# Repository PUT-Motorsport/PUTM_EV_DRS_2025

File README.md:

# PUTM_EV_DRS_2024
 Drs (active aero) project for PUT Motorsport

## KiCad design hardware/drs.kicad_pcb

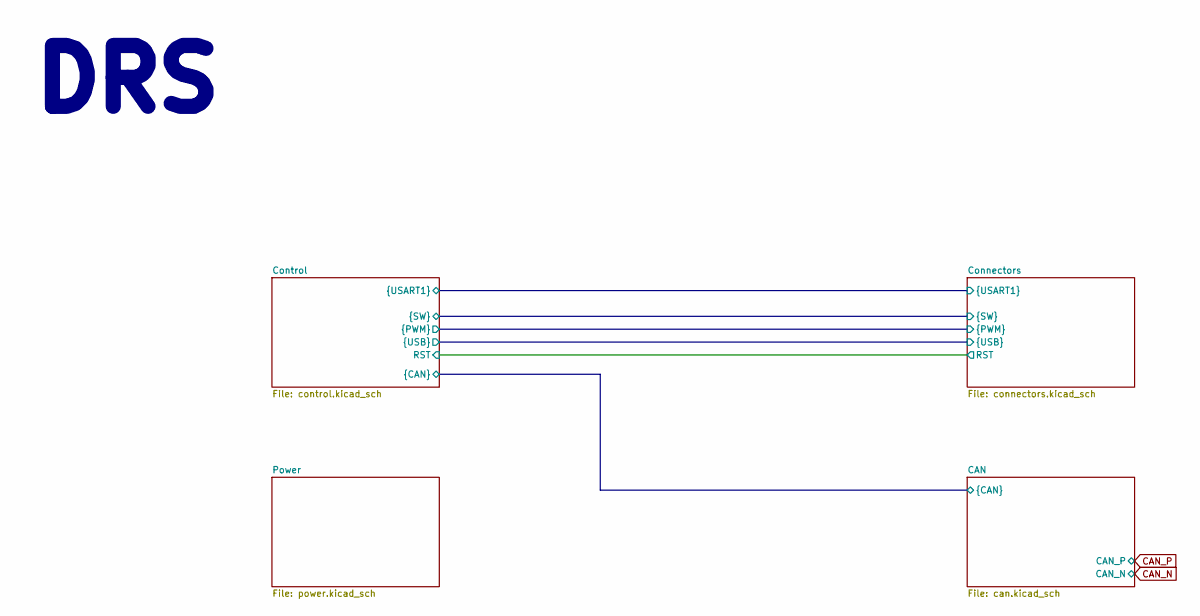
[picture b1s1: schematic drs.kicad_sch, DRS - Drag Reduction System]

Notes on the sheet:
DRS

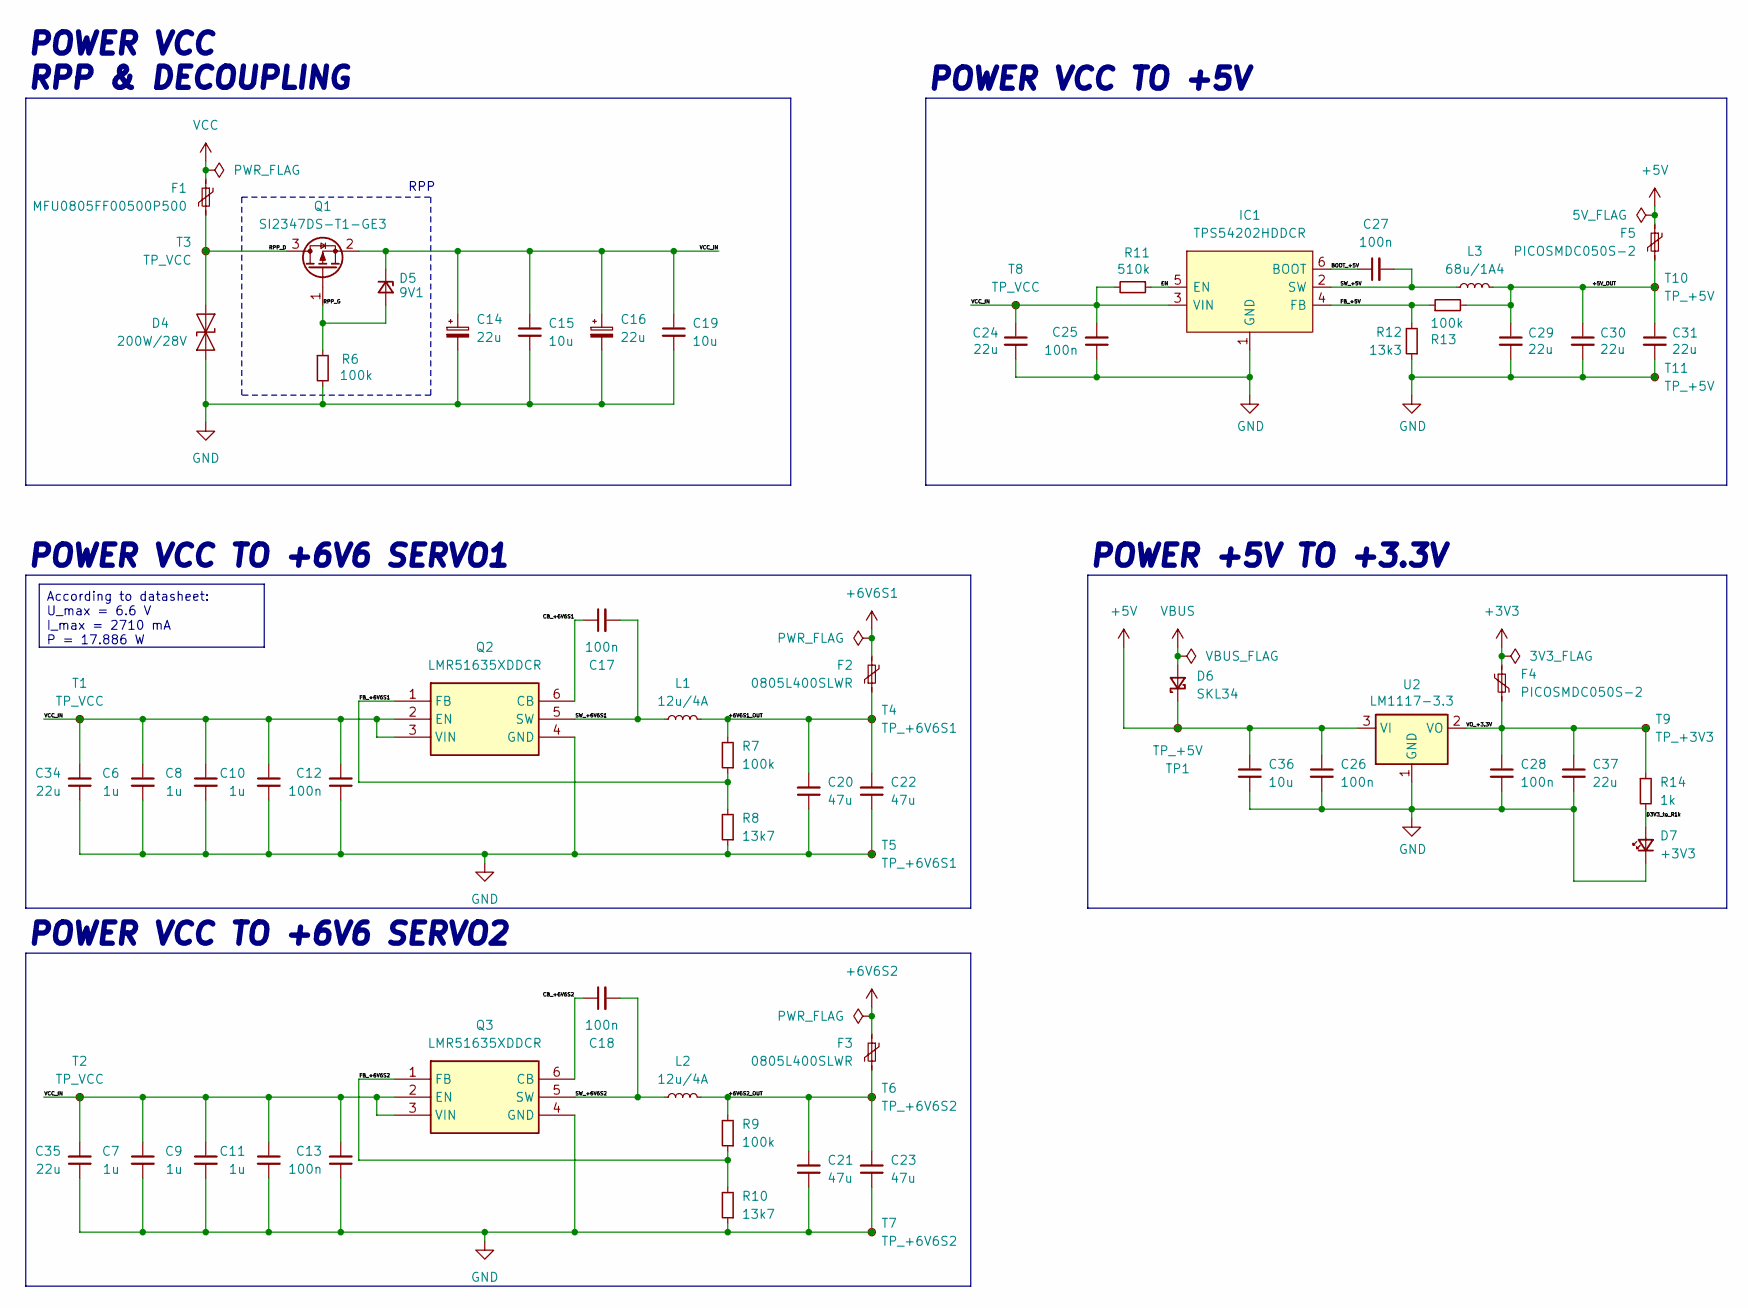
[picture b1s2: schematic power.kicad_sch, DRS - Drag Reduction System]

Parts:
C6, C7, C8, C9, C10, C11: 1u; C_0603_1608Metric_Pad1.08x0.95mm_HandSolder
C12, C13, C17, C18, C26, C27, C28: 100n; C_0603_1608Metric_Pad1.08x0.95mm_HandSolder
C14, C16: 22u; CP_Elec_4x5.8
C15, C19, C36: 10u; C_0603_1608Metric_Pad1.08x0.95mm_HandSolder
C20, C21, C22, C23: 47u; C_0805_2012Metric_Pad1.18x1.45mm_HandSolder
C24, C29, C30, C31: 22u; C_0805_2012Metric_Pad1.18x1.45mm_HandSolder; Manufacturer_Part_Number CL21A107MQYNNWE; Mouser Part Number 810-C2012X5R1V226MAC
C25: 100n; C_0603_1608Metric_Pad1.08x0.95mm_HandSolder; Manufacturer_Part_Number C0603C104J3RACTU; Mouser Part Number 80-C0603C104J3R
C34, C35, C37: 22u; C_0805_2012Metric_Pad1.18x1.45mm_HandSolder
D4: 200W/28V; D_SOD-123
D5: 9V1; D_SOD-323_HandSoldering
D6: SKL34; D_SOD-123F
D7: +3V3; LED_0603_1608Metric_Pad1.05x0.95mm_HandSolder
F1: MFU0805FF00500P500; Fuse_0805_2012Metric_Pad1.15x1.40mm_HandSolder
F2, F3: 0805L400SLWR; Fuse_0805_2012Metric_Pad1.15x1.40mm_HandSolder
F4, F5: PICOSMDC050S-2; Fuse_0805_2012Metric_Pad1.15x1.40mm_HandSolder
IC1: TPS54202HDDCR; SOT-23-6_Handsoldering; Mouser Part Number 595-TPS54202HDDCR
L1, L2: 12u/4A; L_Bourns_SRN6045TA
L3: 68u/1A4; L_TDK_VLS6045EX_VLS6045AF; Mouser Part Number 810-VLS6045EX-680M
Q1: SI2347DS-T1-GE3; SOT-23-3
Q2, Q3: LMR51635XDDCR; SOT-23-6_Handsoldering; Manufacturer_Part_Number LMR51635XDDCR
R6, R7, R9: 100k; R_0603_1608Metric_Pad0.98x0.95mm_HandSolder
R8, R10: 13k7; R_0603_1608Metric_Pad0.98x0.95mm_HandSolder
R11: 510k; R_0603_1608Metric_Pad0.98x0.95mm_HandSolder; Manufacturer_Part_Number RT0603DRD07510KL; Mouser Part Number 603-RT0603DRD07510KL
R12: 13k3; R_0603_1608Metric_Pad0.98x0.95mm_HandSolder; Manufacturer_Part_Number RT0603DRE0713K3L; Mouser Part Number 603-RT0603DRE0713K3L
R13: 100k; R_0603_1608Metric_Pad0.98x0.95mm_HandSolder; Manufacturer_Part_Number RT0603DRE07100KL; Mouser Part Number 603-RT0603DRE07100KL
R14: 1k; R_0603_1608Metric_Pad0.98x0.95mm_HandSolder
T1, T2, T3, T8: TP_VCC; TestPoint_Pad_1.0x1.0mm
T4, T5: TP_+6V6S1; TestPoint_Pad_1.0x1.0mm
T6, T7: TP_+6V6S2; TestPoint_Pad_1.0x1.0mm
T9: TP_+3V3; TestPoint_Pad_1.0x1.0mm
T10, T11: TP_+5V; TestPoint_Pad_1.0x1.0mm
TP1: TP_+5V; TestPoint_Pad_1.0x1.0mm
U2: LM1117-3.3; SOT-223-3_TabPin2

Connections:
+3V3: F4.1; also elsewhere on the board
+5V: C26.1, C36.1, D6.1 (K), F5.1, TP1.1, U2.3 (VI); also elsewhere on the board
+6V6S1: F2.2; also elsewhere on the board
+6V6S2: F3.1; also elsewhere on the board
/Power/+5V_OUT: C29.1, C30.1, C31.1, F5.2, L3.2, R13.2, T10.1
/Power/+6V6S1_OUT: C20.2, C22.2, F2.1, L1.2, R7.2, T4.1
/Power/+6V6S2_OUT: C21.2, C23.2, F3.2, L2.2, R9.2, T6.1
/Power/BOOT_+5V: C27.1, IC1.6 (BOOT)
/Power/CB_+6V6S1: C17.1, Q2.6 (CB)
/Power/CB_+6V6S2: C18.1, Q3.6 (CB)
/Power/D3V3_to_R1k: D7.2 (A), R14.2
/Power/EN: IC1.5 (EN), R11.1
/Power/FB_+5V: IC1.4 (FB), R12.2, R13.1
/Power/FB_+6V6S1: Q2.1 (FB), R7.1, R8.2
/Power/FB_+6V6S2: Q3.1 (FB), R9.1, R10.2
/Power/RPP_D: D4.2 (A2), F1.2, Q1.3 (D), T3.1
/Power/RPP_G: D5.2 (A), Q1.1 (G), R6.1
/Power/SW_+5V: C27.2, IC1.2 (SW), L3.1
/Power/SW_+6V6S1: C17.2, L1.1, Q2.5 (SW)
/Power/SW_+6V6S2: C18.2, L2.1, Q3.5 (SW)
/Power/VCC_IN: C6.1, C7.1, C8.1, C9.1, C10.1, C11.1, C12.2, C13.2, C14.1, C15.1, C16.1, C19.1, C24.1, C25.2, C34.2, C35.2, D5.1 (K), IC1.3 (VIN), Q1.2 (S), Q2.2 (EN), Q2.3 (VIN), Q3.2 (EN), Q3.3 (VIN), R11.2, T1.1, T2.1, T8.1
/Power/VO_+3.3V: C28.1, C37.1, F4.2, R14.1, T9.1, U2.2 (VO)
GND: C6.2, C7.2, C8.2, C9.2, C10.2, C11.2, C12.1, C13.1, C14.2, C15.2, C16.2, C19.2, C20.1, C21.1, C22.1, C23.1, C24.2, C25.1, C26.2, C28.2, C29.2, C30.2, C31.2, C34.1, C35.1, C36.2, C37.2, D4.1 (A1), D7.1 (K), IC1.1 (GND), Q2.4 (GND), Q3.4 (GND), R6.2, R8.1, R10.1, R12.1, T5.1, T7.1, T11.1, U2.1 (GND); also elsewhere on the board
VBUS: D6.2 (A); also elsewhere on the board
VCC: F1.1; also elsewhere on the board

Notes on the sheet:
RPP
POWER VCC TO +6V6 SERVO2
POWER VCC TO +5V
POWER +5V TO +3.3V
POWER VCC RPP & DECOUPLING
POWER VCC TO +6V6 SERVO1
According to datasheet: U_max = 6.6 V I_max = 2710 mA P = 17.886 W

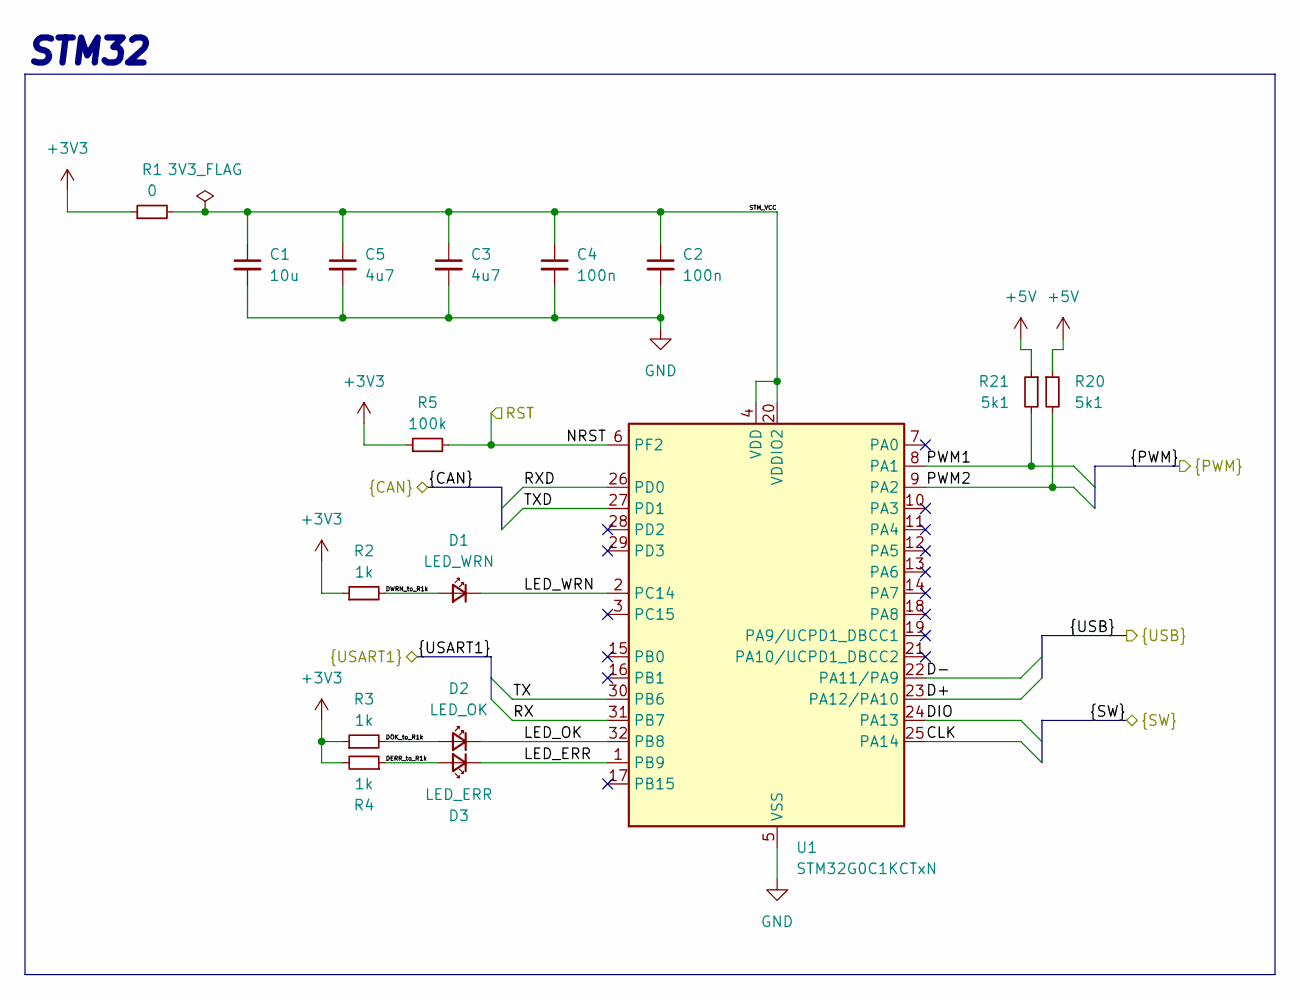
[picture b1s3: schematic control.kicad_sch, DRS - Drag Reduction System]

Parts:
C1: 10u; C_0603_1608Metric_Pad1.08x0.95mm_HandSolder
C2, C4: 100n; C_0603_1608Metric_Pad1.08x0.95mm_HandSolder
C3, C5: 4u7; C_0603_1608Metric_Pad1.08x0.95mm_HandSolder
D1: LED_WRN; LED_0603_1608Metric_Pad1.05x0.95mm_HandSolder
D2: LED_OK; LED_0603_1608Metric_Pad1.05x0.95mm_HandSolder
D3: LED_ERR; LED_0603_1608Metric_Pad1.05x0.95mm_HandSolder
R1: 0; R_0603_1608Metric_Pad0.98x0.95mm_HandSolder
R2, R3, R4: 1k; R_0603_1608Metric_Pad0.98x0.95mm_HandSolder
R5: 100k; R_0603_1608Metric_Pad0.98x0.95mm_HandSolder
R20, R21: 5k1; R_0603_1608Metric_Pad0.98x0.95mm_HandSolder
U1: STM32G0C1KCTxN; LQFP-32_7x7mm_P0.8mm

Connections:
+3V3: R1.1, R2.1, R3.1, R4.2, R5.1; also elsewhere on the board
+5V: R20.1, R21.1; also elsewhere on the board
/CAN/RXD: U1.26 (PD0); also elsewhere on the board
/CAN/TXD: U1.27 (PD1); also elsewhere on the board
/Connectors/CLK: U1.25 (PA14); also elsewhere on the board
/Connectors/D+: U1.23 (PA12/PA10); also elsewhere on the board
/Connectors/D-: U1.22 (PA11/PA9); also elsewhere on the board
/Connectors/DIO: U1.24 (PA13); also elsewhere on the board
/Connectors/PWM1: R21.2, U1.8 (PA1); also elsewhere on the board
/Connectors/PWM2: R20.2, U1.9 (PA2); also elsewhere on the board
/Connectors/RX: U1.31 (PB7); also elsewhere on the board
/Connectors/TX: U1.30 (PB6); also elsewhere on the board
/Control/DERR_to_R1k: D3.2 (A), R4.1
/Control/DOK_to_R1k: D2.2 (A), R3.2
/Control/DWRN_to_R1k: D1.2 (A), R2.2
/Control/LED_ERR: D3.1 (K), U1.1 (PB9)
/Control/LED_OK: D2.1 (K), U1.32 (PB8)
/Control/LED_WRN: D1.1 (K), U1.2 (PC14)
/Control/NRST: R5.2, U1.6 (PF2); also elsewhere on the board
/Control/STM_VCC: C1.1, C2.1, C3.1, C4.1, C5.1, R1.2, U1.4 (VDD), U1.20 (VDDIO2)
GND: C1.2, C2.2, C3.2, C4.2, C5.2, U1.5 (VSS); also elsewhere on the board

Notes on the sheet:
STM32

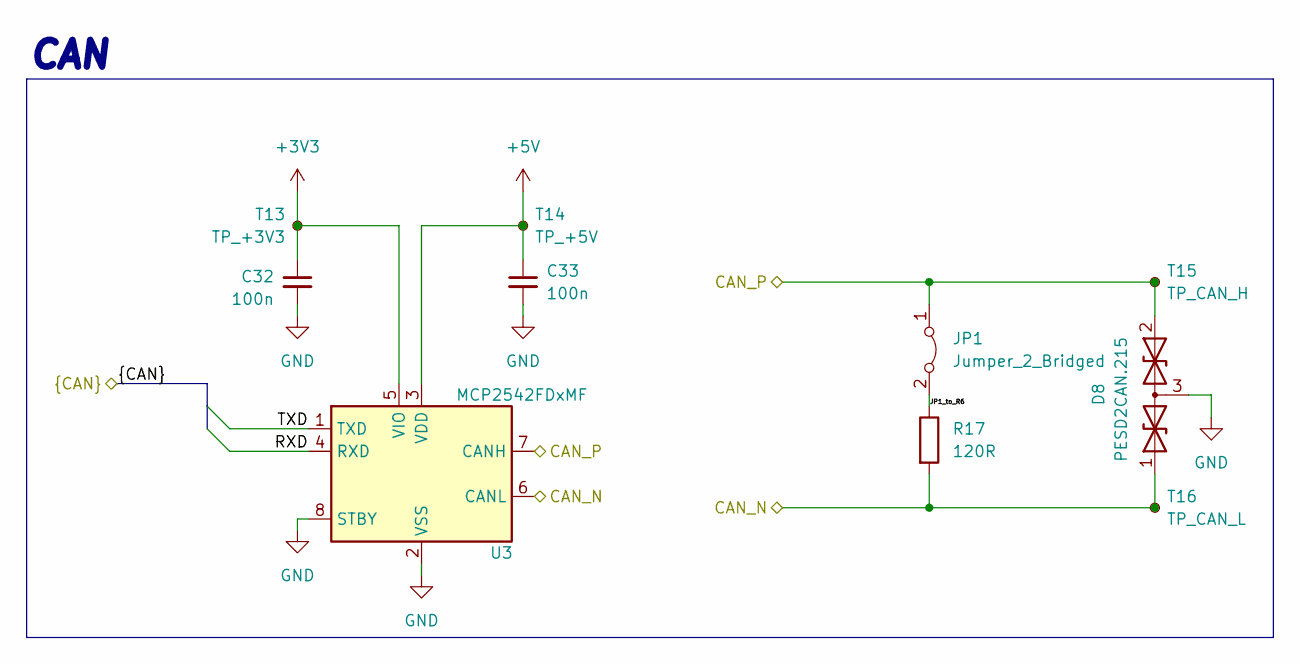
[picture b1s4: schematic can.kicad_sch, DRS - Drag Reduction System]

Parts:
C32, C33: 100n; C_0603_1608Metric_Pad1.08x0.95mm_HandSolder
D8: PESD2CAN.215; SOT-23-3
JP1: Jumper_2_Bridged; PinHeader_1x02_P2.54mm_Vertical
R17: 120R; R_0603_1608Metric_Pad0.98x0.95mm_HandSolder
T13: TP_+3V3; TestPoint_Pad_1.0x1.0mm
T14: TP_+5V; TestPoint_Pad_1.0x1.0mm
T15: TP_CAN_H; TestPoint_Pad_1.0x1.0mm
T16: TP_CAN_L; TestPoint_Pad_1.0x1.0mm
U3: MCP2542FDxMF; DFN-8-1EP_3x3mm_P0.65mm_EP1.55x2.4mm

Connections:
+3V3: C32.1, T13.1, U3.5 (VIO); also elsewhere on the board
+5V: C33.1, T14.1, U3.3 (VDD); also elsewhere on the board
/CAN/JP1_to_R6: JP1.2 (B), R17.1
/CAN/RXD: U3.4 (RXD); also elsewhere on the board
/CAN/TXD: U3.1 (TXD); also elsewhere on the board
CAN_N: D8.1 (A1), R17.2, T16.1, U3.6 (CANL); also elsewhere on the board
CAN_P: D8.2 (A2), JP1.1 (A), T15.1, U3.7 (CANH); also elsewhere on the board
GND: C32.2, C33.2, D8.3 (common), U3.2 (VSS), U3.8 (STBY), U3.9 (VSS); also elsewhere on the board

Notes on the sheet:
CAN

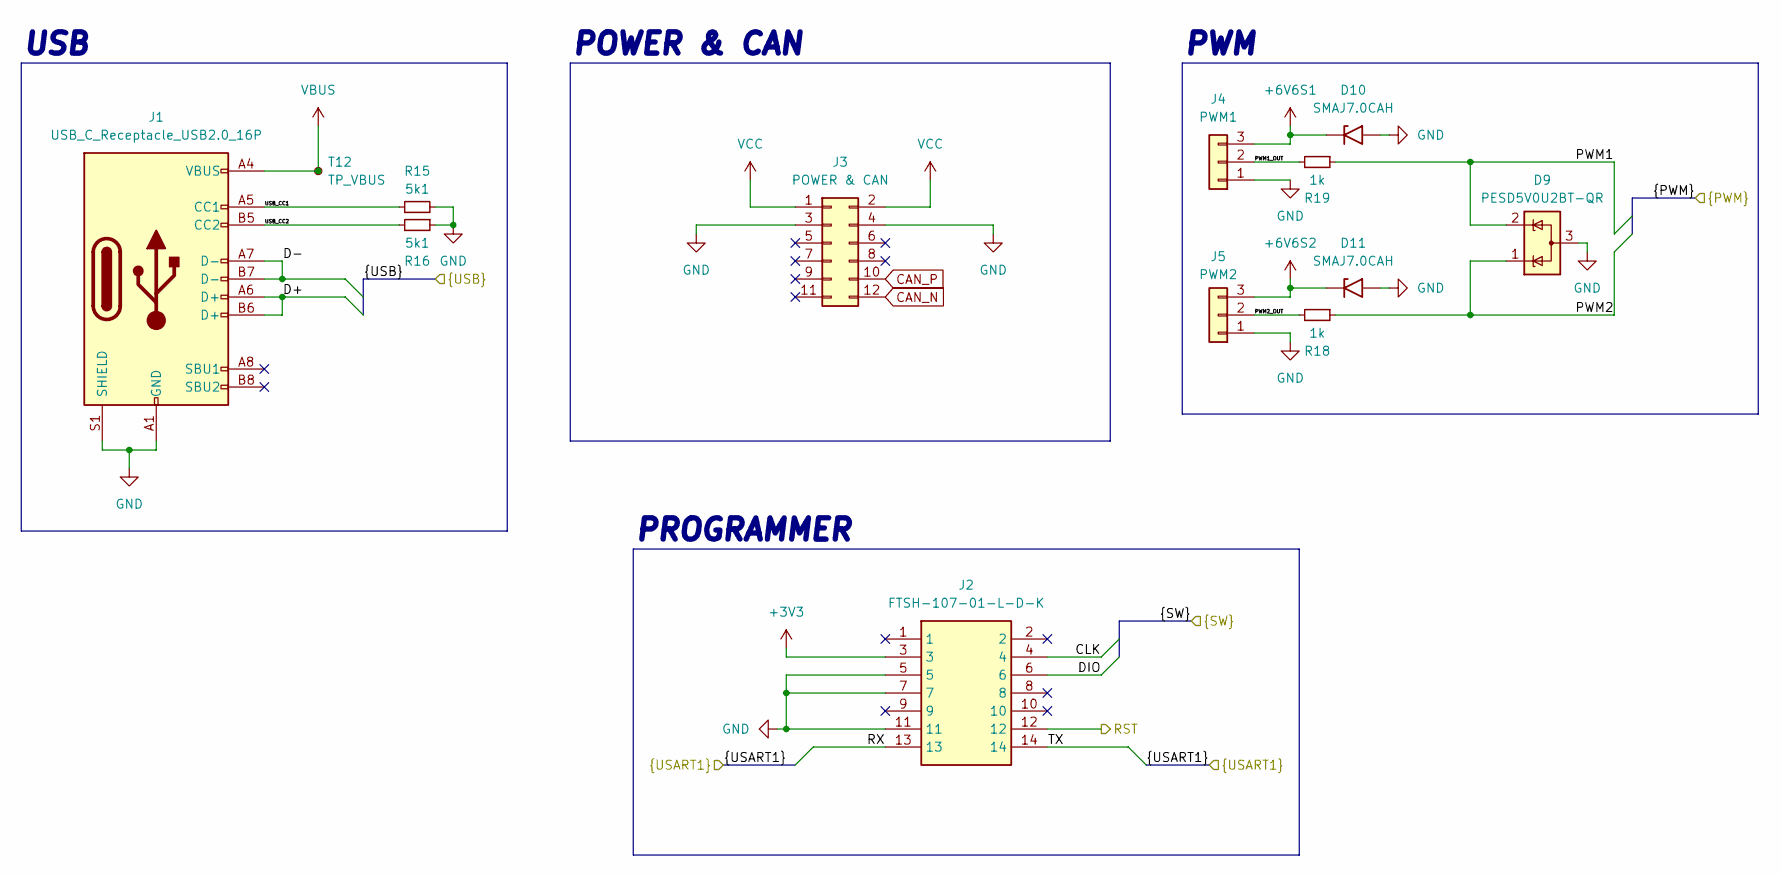
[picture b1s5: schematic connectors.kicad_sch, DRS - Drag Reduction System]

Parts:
D9: PESD5V0U2BT-QR; SOT-23-3
D10, D11: SMAJ7.0CAH; D_SMA_Handsoldering
J1: USB_C_Receptacle_USB2.0_16P; USB_C_Receptacle_GCT_USB4105-xx-A_16P_TopMnt_Horizontal
J2: FTSH-107-01-L-D-K; FTSH-107-XX-YYY-D-K; Mouser Part Number 200-FTSH10701LDK
J3: POWER & CAN; SHDR12W64P254X254_2X6_2286X895X915P
J4: PWM1; HDRV3W64P0X254_1X3_762X254X864P
J5: PWM2; HDRV3W64P0X254_1X3_762X254X864P
R15, R16: 5k1; R_0603_1608Metric_Pad0.98x0.95mm_HandSolder
R18, R19: 1k; R_0603_1608Metric_Pad0.98x0.95mm_HandSolder
T12: TP_VBUS; TestPoint_Pad_1.0x1.0mm

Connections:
+3V3: J2.3; also elsewhere on the board
+6V6S1: D10.1 (A1), J4.3; also elsewhere on the board
+6V6S2: D11.1 (A1), J5.3; also elsewhere on the board
/Connectors/CLK: J2.4; also elsewhere on the board
/Connectors/D+: J1.A6 (D+), J1.B6 (D+); also elsewhere on the board
/Connectors/D-: J1.A7 (D-), J1.B7 (D-); also elsewhere on the board
/Connectors/DIO: J2.6; also elsewhere on the board
/Connectors/PWM1: D9.2 (K), R19.1; also elsewhere on the board
/Connectors/PWM1_OUT: J4.2, R19.2
/Connectors/PWM2: D9.1 (K), R18.1; also elsewhere on the board
/Connectors/PWM2_OUT: J5.2, R18.2
/Connectors/RX: J2.13; also elsewhere on the board
/Connectors/TX: J2.14; also elsewhere on the board
/Connectors/USB_CC1: J1.A5 (CC1), R15.1
/Connectors/USB_CC2: J1.B5 (CC2), R16.2
/Control/NRST: J2.12; also elsewhere on the board
CAN_N: J3.12; also elsewhere on the board
CAN_P: J3.10; also elsewhere on the board
GND: D9.3 (A), D10.2 (A2), D11.2 (A2), J1.A1 (GND), J1.A12 (GND), J1.B1 (GND), J1.B12 (GND), J1.S1 (SHIELD), J2.5, J2.7, J2.11, J3.3, J3.4, J4.1, J5.1, R15.2, R16.1; also elsewhere on the board
VBUS: J1.A4 (VBUS), J1.A9 (VBUS), J1.B4 (VBUS), J1.B9 (VBUS), T12.1; also elsewhere on the board
VCC: J3.1, J3.2; also elsewhere on the board

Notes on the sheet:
PWM
PROGRAMMER
POWER & CAN
USB

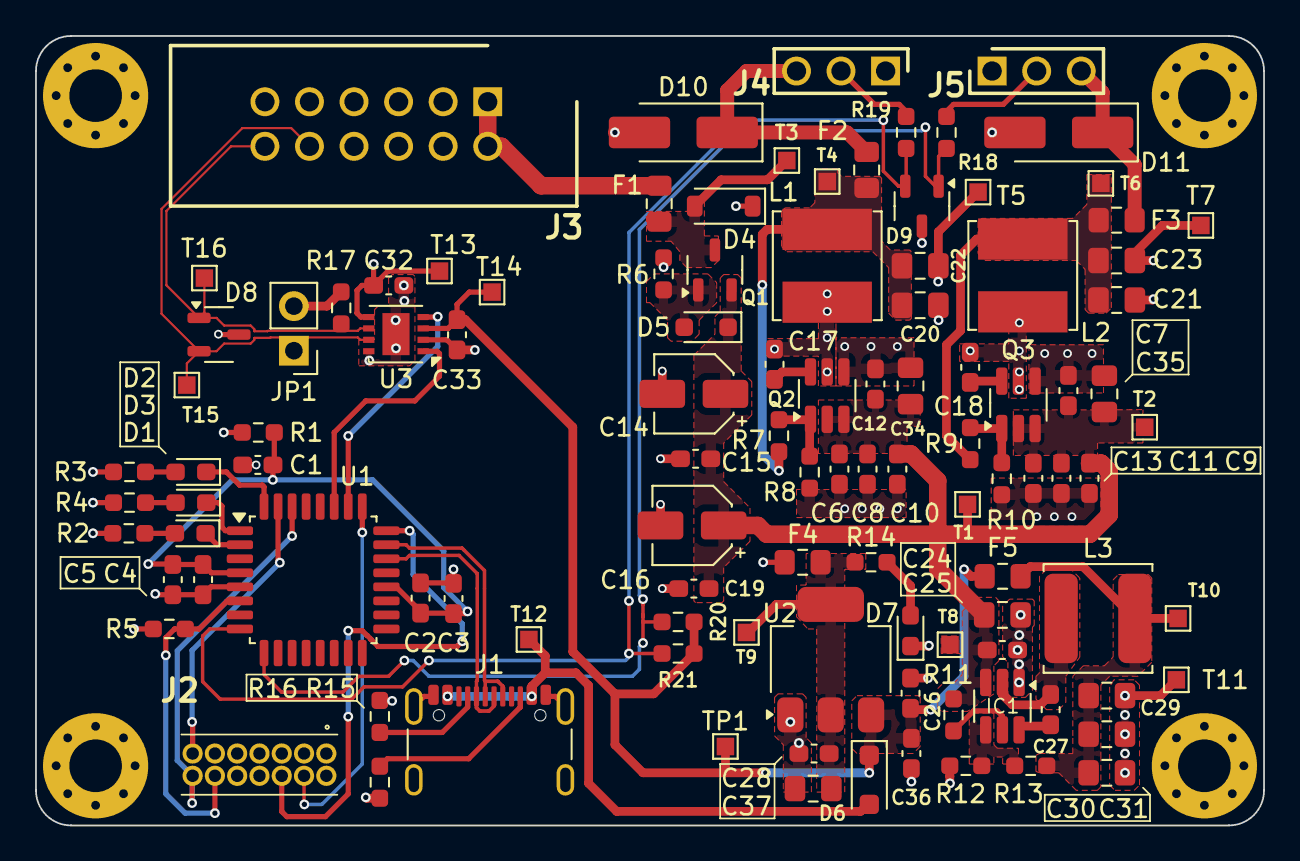
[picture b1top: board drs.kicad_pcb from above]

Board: 4 copper layers, 70.0 x 45.0 mm, 107 parts (0 on the bottom side), 50 nets.

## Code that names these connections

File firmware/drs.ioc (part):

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Mcu.Name=STM32G0C1K(C-E)TxN
Mcu.Package=LQFP32
Mcu.UserName=STM32G0C1KCTxN
PA1.Signal=S_TIM2_CH2
PA2.Signal=S_TIM2_CH3
PA5.Mode=Asynchronous
PA5.Signal=USART3_TX
PA7.Signal=S_TIM3_CH2
PB0.Mode=Asynchronous
PB0.Signal=USART3_RX
PB8.GPIOParameters=GPIO_Label
PB8.GPIO_Label=LED_OK
PB8.Signal=GPIO_Output
PB9.GPIOParameters=GPIO_Label
PB9.GPIO_Label=LED_ERR
PB9.Signal=GPIO_Output
PC14-OSC32_IN\ (PC14).GPIOParameters=PinState,GPIO_Label
PC14-OSC32_IN\ (PC14).GPIO_Label=LED_WRN
PC14-OSC32_IN\ (PC14).PinState=GPIO_PIN_RESET
PC14-OSC32_IN\ (PC14).Signal=GPIO_Output
PD0.GPIOParameters=GPIO_Speed
PD0.GPIO_Speed=GPIO_SPEED_FREQ_VERY_HIGH
PD0.Mode=FDCAN_Activate
PD0.Signal=FDCAN1_RX
PD1.GPIOParameters=GPIO_Speed
PD1.GPIO_Speed=GPIO_SPEED_FREQ_VERY_HIGH
PD1.Mode=FDCAN_Activate
PD1.Signal=FDCAN1_TX
RCC.HSE_VALUE=8000000
RCC.SYSCLKFreq_VALUE=16000000
board=custom

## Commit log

2025-01-09 DRS-first commit
2025-01-09 values-correction
2025-01-14 added sheet pins
2025-01-14 documentation update
2025-01-21 added 6V6 for servo
2025-01-21 power labels corrected
2025-01-21 connectors - added, buses - todo
2025-02-11 Poprawione busy, brak errorow
2025-02-18 Footprints addes beside PWM connectors
2025-02-18 PWM conns added
2025-02-19 Table updated- fuses and conns still not added
2025-02-19 All footprints added
2025-03-09 pcb scheme update - general/basic aligment
2025-03-17 Items assebled
2025-03-25 Wszystkie elementy poukładane według dokumentacji na pod-grupy
2025-03-25 nowy uklad
2025-04-01 schematic & pcb update
2025-04-02 schematic & pcb udpate
2025-04-05 pcb update
2025-04-05 signal routing
2025-04-05 usbc changed, foots for electro cap and +5 lay
2025-04-06 pcb & footprint update
2025-04-06 d4 - footprint change
2025-04-06 VCC to RPP & RPP to rest routing
2025-04-08 pcb dp update
2025-04-08 pcb can & usb update
2025-04-10 pcb update - testpoints & 3V3
2025-05-05 silkscreen update
2025-05-06 pcb & scheme update
2025-05-07 psb & schematic update
2025-05-21 Added author on pcb
2025-05-25 working version cokolwiek
2025-05-25 Add git module file
2025-05-25 Add can lib
2025-05-27 work version
2025-05-27 project form c to cpp
2025-05-28 Add CAN data receive
    *Issue with lib include
2025-06-02 New stm, changed canfd, working CAN lib
2025-06-02 add git modules and can lib
2025-08-12 Nowy program do drsa - builduje sie do testow
2025-08-12 usunieto submodul
2025-08-12 submodule dodany na nowo
2025-08-15 kwazer nie pokazuje bledu - servo dalej nie dziala
2025-09-21 Jakies poprawki - dalej nie dziala
